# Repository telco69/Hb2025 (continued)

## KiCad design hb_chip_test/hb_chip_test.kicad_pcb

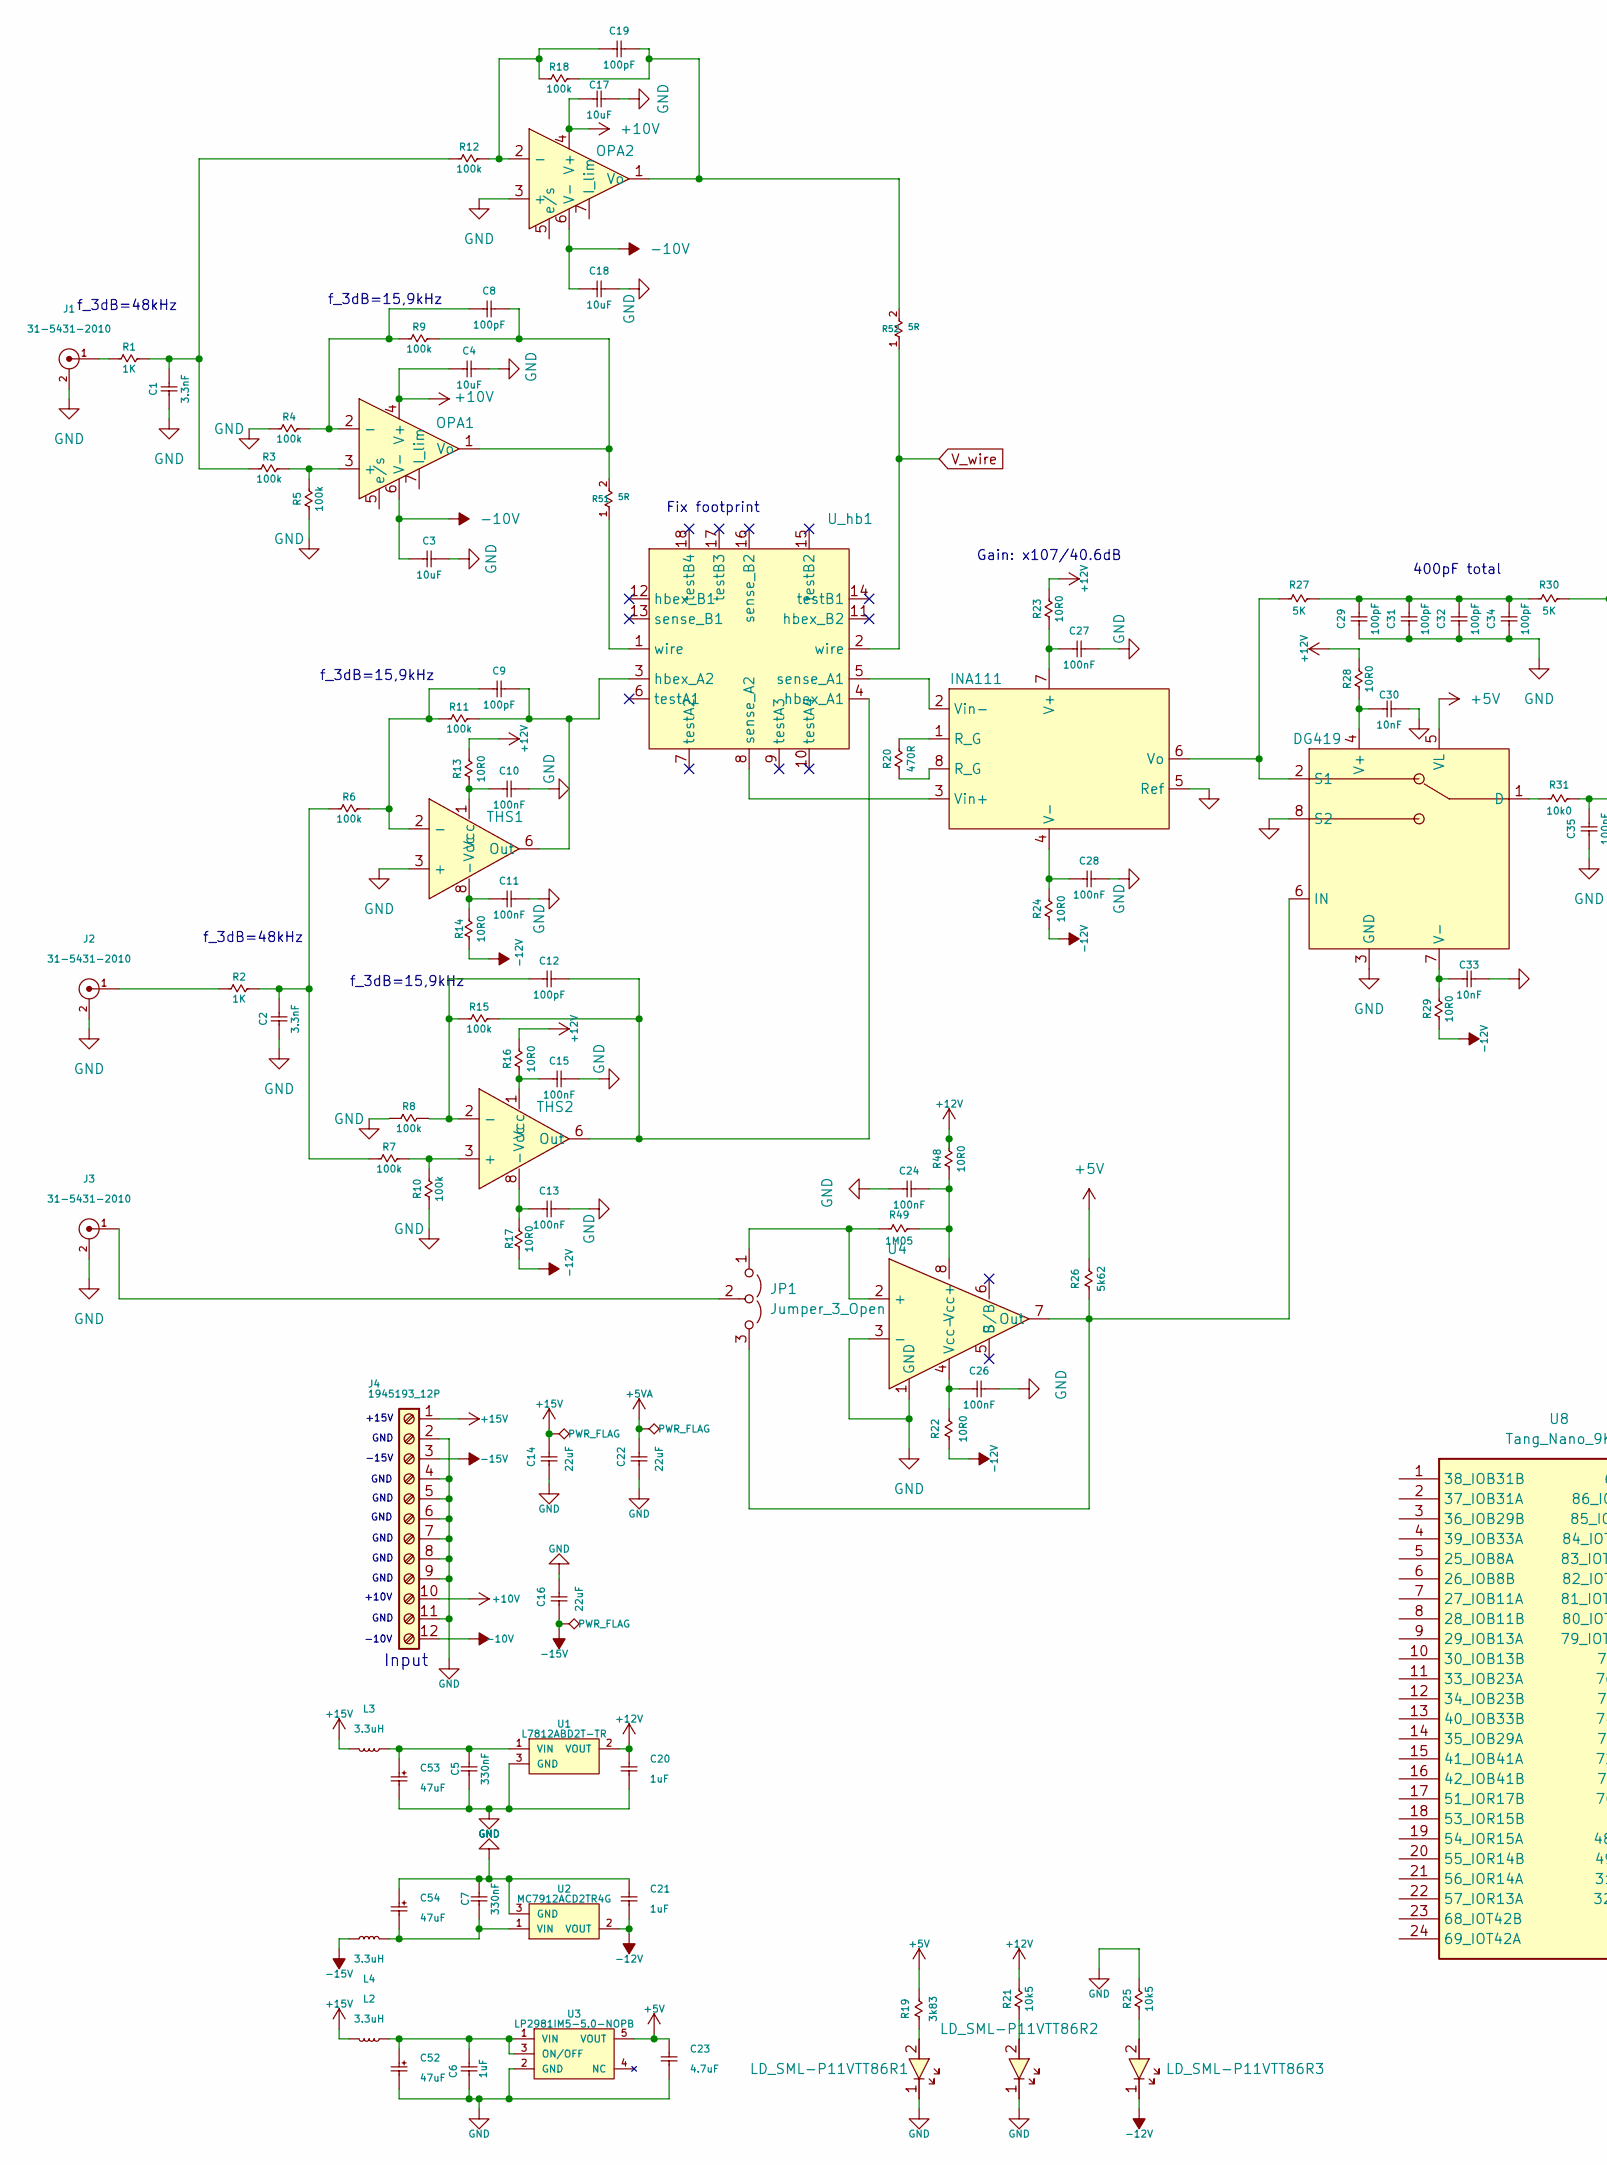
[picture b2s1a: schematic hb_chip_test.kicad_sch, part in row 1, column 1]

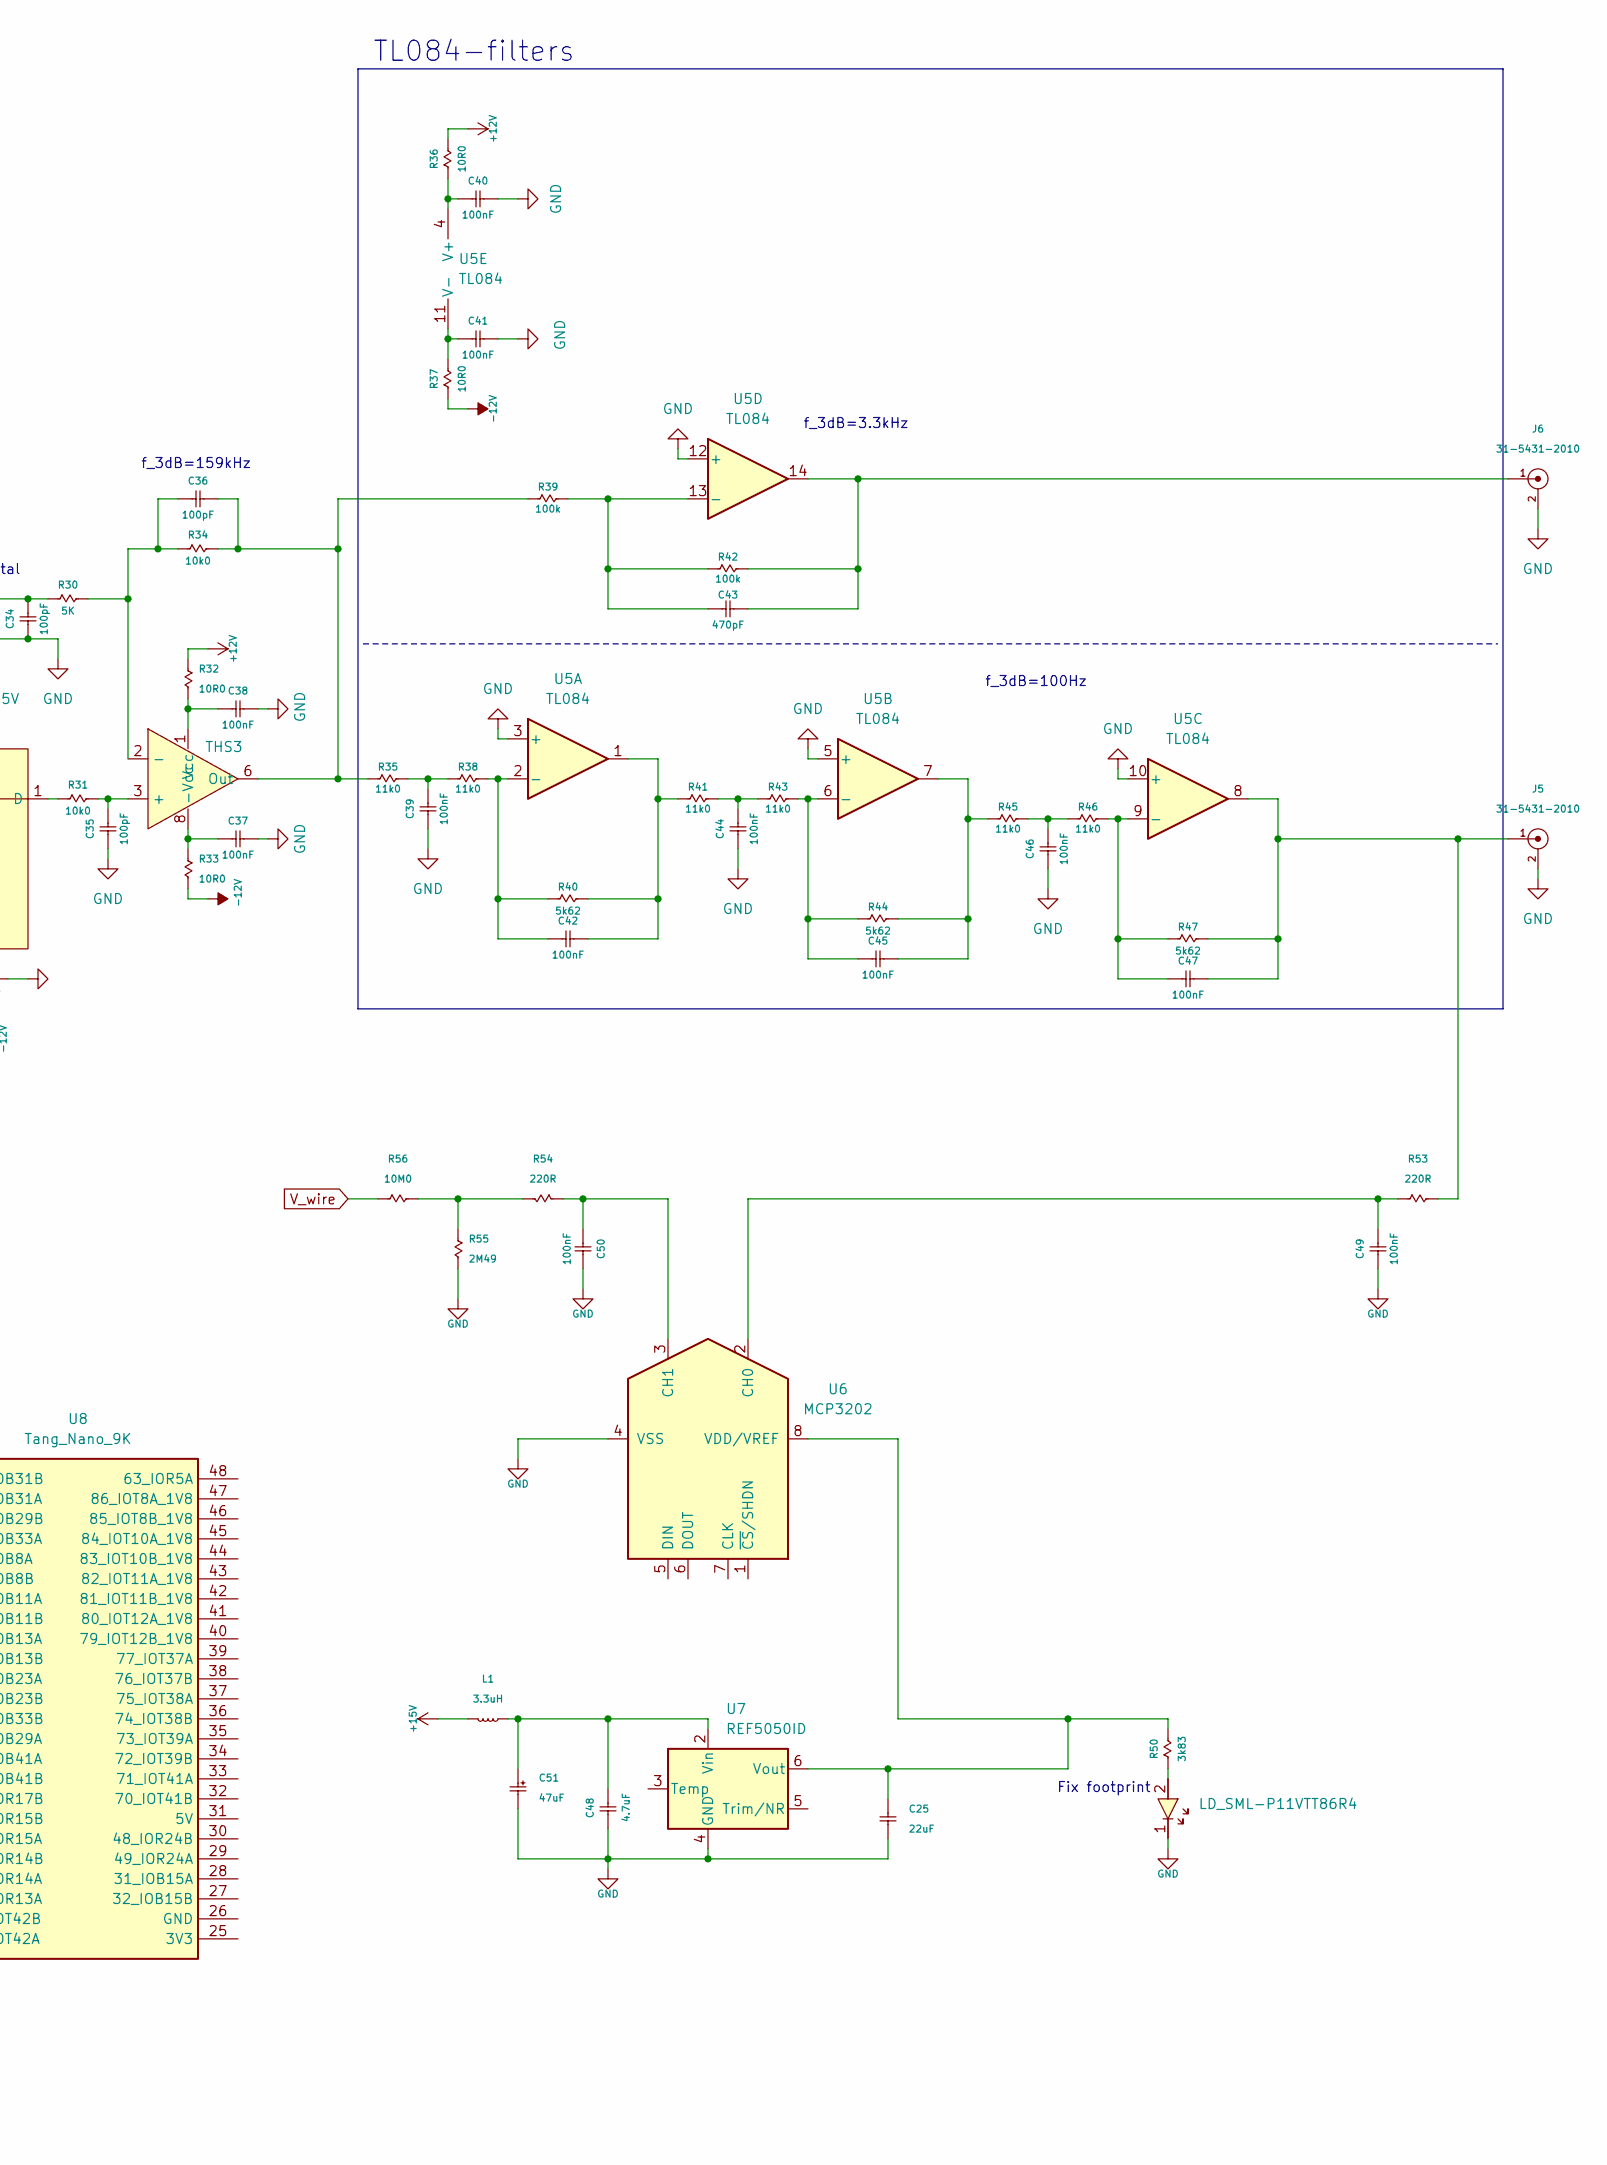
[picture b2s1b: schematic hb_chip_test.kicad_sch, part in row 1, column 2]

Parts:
C1, C2: C_0402_3.3nF_16V_X7R_CID1.2.2599; C0402_CAPC100X50X61L25N; Tolerance 5.0 %; Voltage 16.0 V; MPN 0402YC332JAT2A
C3, C4, C17, C18: C_2220_10uF_50V_X7R_CID1.2.4299; C2220_CAPC570X500X270L60N; Tolerance 5.0 %; Voltage 50.0 V; MPN 22205C106JAT2A
C5, C7: C_0805_330nF_50V_X7R_CID1.2.632; C0805_CAPC200X125X130L45N; MPN CL21B334KBFNNNE
C6, C20, C21: C_0805_1uF_16V_X7R_CID1.2.3095; C0805_CAPC200X125X130L45N; Tolerance 5.0 %; Voltage 16.0 V; MPN 0805YC105JAT2A
C8, C9, C12, C19, C29, C31, C32, C34, C35, C36: C_0402_100pF_50V_C0G_CID1.2.681; C0402_CAPC100X50X61L25N; Tolerance 5.0 %; Voltage 50.0 V; MPN 04025A101JAT2A
C10, C11, C13, C15, C24, C26, C27, C28, C37, C38, C39, C40, C41, C42, C44, C45, C46, C47, C49, C50: C_0805_100nF_16V_X7R_CID1.2.3078; C0805_CAPC200X125X130L45N; Tolerance 5.0 %; Voltage 16.0 V; MPN 0805YC104JAT2A
C14, C16, C22, C25: C_2220_22uF_25V_X7R_CID1.2.4254; C2220_CAPC570X500X270L60N; Tolerance 5.0 %; Voltage 25.0 V; MPN 22203C226JAT2A
C23, C48: C_1812_4.7uF_25V_X7R_CID1.2.4026; C1812_CAPC450X320X280L60N; Tolerance 5.0 %; Voltage 25.0 V; MPN 18123C475JAT2A
C30, C33: C_0402_10nF_16V_X7R_CID1.2.2607; C0402_CAPC100X50X61L25N; Tolerance 5.0 %; Voltage 16.0 V; MPN 0402YC103JAT2A
C43: C_0402_470pF_50V_C0G_CID1.2.184; C0402_CAPC100X50X61L25N; Capacitance Tolerance ±5%; Voltage Rating (DC) 50.0 V; MPN GCM1555C1H471JA16D
C51, C52, C53, C54: C_2917_47uF_20V_20%_CID1.3.892; C2917_CAPC730X430X310L130N; MPN 20TQC47MYFT
DG419: SOIC-8_3.9x4.9mm_P1.27mm
INA111: SMDIP-8_W9.53mm
J1, J2, J3, J5, J6: 31-5431-2010_CID2.5.196; AMPHENOL_31-5431-2010; MPN 31-5431-2010
J4: 1945193_12P_CID2.2.928; PHOENIX_1945193_12P; MPN 1945193_12P
JP1: Jumper_3_Open; 2_WAY_SOLDER_JUMPER
L1, L2, L3, L4: L_3.3uH_870mA_CID7.3.944; L0805_INDC200X125X140L50N; MPN BRC2012T3R3MD
LD_SML-P11VTT86R1, LD_SML-P11VTT86R2, LD_SML-P11VTT86R3, LD_SML-P11VTT86R4: SML_P11; MPN SML-P11VTT86R
OPA1, OPA2: TO-220-7_P2.54x3.8mm_StaggerOdd_Lead5.85mm_TabDown
R1, R2: R_0805_1K_CID10.99.611; R0805_RESC200X125X50L35N; MPN Y16291K00000B9R
R3, R4, R5, R6, R7, R8, R9, R10, R11, R12, R15, R18, R39, R42: R_0805_100k_CID10.9.5903; R0805_RESC200X125X50L35N; Tolerance 1.0 %; Voltage 50.0 V; MPN CRCW0805100KFKEA
R13, R14, R16, R17, R22, R23, R24, R28, R29, R32, R33, R36, R37, R48: R_0805_10R0_CID10.9.4757; R0805_RESC200X125X50L35N; Tolerance 1.0 %; Voltage 50.0 V; MPN 40010260210R0F4
R19, R50: R_0805_3k83_CID10.9.461; R0805_RESC200X125X50L35N; Power Rating 125.0 mW; Resistance Tolerance ±1%; MPN CRCW08053K83FKEA
R20: R_0402_470R_CID10.9.70; R0402_RESC100X50X37L20N; Power Rating 100.0 mW; Resistance Tolerance ±1%; MPN ERJ-2RKF4700X
R21, R25: R_0805_10k5_CID10.9.5868; R0805_RESC200X125X50L35N; Tolerance 1.0 %; Voltage 50.0 V; MPN CRCW080510K5FKEA
R26, R40, R44, R47: R_0805_5k62_CID10.9.159; R0805_RESC200X125X50L35N; Power Rating 125.0 mW; Resistance Tolerance ±1%; MPN CRCW08055K62FKEA
R27, R30: R_0805_5K_CID10.99.612; R0805_RESC200X125X50L35N; MPN Y16295K00000T9R
R31, R34: R_0805_10k0_CID10.9.476; R0805_RESC200X125X50L35N; Power Rating 125.0 mW; Resistance Tolerance ±1%; MPN CRCW080510K0FKEA
R35, R38, R41, R43, R45, R46: R_0805_11k0_CID10.9.5869; R0805_RESC200X125X50L35N; Tolerance 1.0 %; Voltage 50.0 V; MPN CRCW080511K0FKEA
R49: R_0805_1M05_CID10.9.5947; R0805_RESC200X125X50L35N; Tolerance 1.0 %; Voltage 50.0 V; MPN CRCW08051M05FKEA
R51, R52: 5R; TO-220-2_Horizontal_TabDown; MPN PWR220T-35-5R00F
R53, R54: R_0805_220R_CID10.9.602; R0805_RESC200X125X50L35N; Power Rating 125.0 mW; Resistance Tolerance ±1%; MPN CRCW0805220RFKEAHP
R55: R_0805_2M49_CID10.9.5964; R0805_RESC200X125X50L35N; Tolerance 1.0 %; Voltage 50.0 V; MPN CRCW08052M49FKEA
R56: R_0805_10M0_CID10.9.5993; R0805_RESC200X125X50L35N; Tolerance 1.0 %; Voltage 50.0 V; MPN CRCW080510M0FKEA
THS1, THS2, THS3: SOIC-8_3.9x4.9mm_P1.27mm
U1: L7812ABD2T-TR_CID8.52.934; DPAK3P508_1419X457L172X97T635X1023N; MPN L7812ABD2T-TR
U2: MC7912ACD2TR4G_CID8.52.429; DPAK3P508_1419X457L172X97T635X1023N; MPN MC7912ACD2TR4G
U3: LP2981IM5-5.0-NOPB_CID8.52.176; SOT23-5P95_270X145L35X35N; Current Rating 100.0mA; Dropout Voltage 200.0mV; MPN LP2981IM5-5.0-NOPB
U4: SO-8_3.9x4.9mm_P1.27mm; MPN LM311DT
U5: TL084; SOIC-14_3.9x8.7mm_P1.27mm
U6: MCP3202; SOIC-8_3.9x4.9mm_P1.27mm
U7: REF5050ID; SOIC-8_3.9x4.9mm_P1.27mm
U8: Tang_Nano_9K; DIP-48_TangNano9K
U_hb1: (no value)

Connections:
+5V: C23.1, DG419.5 (VL), R19.2, R26.2, U3.5 (VOUT); also elsewhere on the board
+5VA: C22.2
+10V: C4.1, C17.1, J4.10, OPA1.4 (V+), OPA2.4 (V+)
+12V: C20.1, R13.2, R16.2, R21.2, R23.2, R28.2, R32.1, R36.2, R48.2, U1.2 (VOUT)
+15V: C14.2, J4.1, L1.1, L2.1, L3.1
-10V: C3.1, C18.1, J4.12, OPA1.6 (V-), OPA2.6 (V-)
-12V: C21.2, LD_SML-P11VTT86R3.1, R14.1, R17.1, R22.1, R24.1, R29.1, R33.2, R37.1, U2.2 (VOUT)
-15V: C16.1, J4.3, L4.1
GND: C1.1, C2.1, C3.2, C4.2, C5.1, C6.2, C7.2, C10.2, C11.2, C13.2, C14.1, C15.2, C16.2, C17.2, C18.2, C20.2, C21.1, C22.1, C23.2, C24.1, C25.2, C26.2, C27.2, C28.2, C29.1, C30.2, C31.1, C32.1, C33.2, C34.1, C35.1, C37.2, C38.2, C39.1, C40.2, C41.2, C44.1, C46.1, C48.2, C49.1, C50.1, C51.2, C52.2, C53.2, C54.1, DG419.3 (GND), DG419.8 (S2), INA111.5 (Ref), J1.2, J2.2, J3.2, J4.2, J4.4, J4.5, J4.6, J4.7, J4.8, J4.9, J4.11, J5.2, J6.2, LD_SML-P11VTT86R1.1, LD_SML-P11VTT86R2.1, LD_SML-P11VTT86R4.1, OPA2.3 (+), R4.1, R5.1, R10.1, R25.2, R55.2, THS1.3 (+), U1.3 (GND), U2.3 (GND), U3.2 (GND), U4.1 (GND), U4.3 (-), U5.3 (+), U5.5 (+), U5.10 (+), U5.12 (+), U6.4 (VSS), U7.4 (GND)
unnamed: C1.2, R1.2, R3.1, R12.1
unnamed: C2.2, R2.2, R6.1, R7.1
unnamed: C29.2, C31.2, C32.2, C34.2, R27.2, R30.1
unnamed: C39.2, R35.2, R38.1
unnamed: C42.2, R40.2, R41.1, U5.1
unnamed: C43.2, J6.1, R42.2, U5.14
unnamed: C44.2, R41.2, R43.1
unnamed: C45.2, R44.2, R45.1, U5.7
unnamed: C46.2, R45.2, R46.1
unnamed: C47.2, J5.1, R47.2, R53.2, U5.8
unnamed: DG419.1 (D), R31.1
unnamed: DG419.6 (IN), JP1.3 (B), R26.1, U4.7 (Out)
unnamed: DG419.2 (S1), INA111.6 (Vo), R27.1
unnamed: C30.1, DG419.4 (V+), R28.1
unnamed: C33.1, DG419.7 (V-), R29.2
unnamed: INA111.1 (R_G), R20.2
unnamed: INA111.8 (R_G), R20.1
unnamed: C27.1, INA111.7 (V+), R23.1
unnamed: C28.1, INA111.4 (V-), R24.2
unnamed: INA111.3 (Vin+), U_hb1.8 (sense_A2)
unnamed: INA111.2 (Vin-), U_hb1.5 (sense_A1)
unnamed: J1.1, R1.1
unnamed: J2.1, R2.1
unnamed: JP1.1 (A), R49.1, U4.2 (+)
unnamed: J3.1, JP1.2 (C)
unnamed: LD_SML-P11VTT86R1.2, R19.1
unnamed: LD_SML-P11VTT86R2.2, R21.1
unnamed: LD_SML-P11VTT86R3.2, R25.1
unnamed: LD_SML-P11VTT86R4.2, R50.1
unnamed: OPA1.3 (+), R3.2, R5.2
unnamed: C8.1, OPA1.2 (-), R4.2, R9.1
unnamed: C8.2, OPA1.1 (Vo), R9.2, R51.2
unnamed: C19.1, OPA2.2 (-), R12.2, R18.1
unnamed: C19.2, OPA2.1 (Vo), R18.2, R52.2
unnamed: R51.1, U_hb1.1 (wire)
unnamed: R54.2, R55.1, R56.2
unnamed: C9.1, R6.2, R11.1, THS1.2 (-)
unnamed: C11.1, R14.2, THS1.8 (-Vcc)
unnamed: C9.2, R11.2, THS1.6 (Out), U_hb1.3 (hbex_A2)
unnamed: C10.1, R13.1, THS1.1 (Vcc)
unnamed: R7.2, R10.2, THS2.3 (+)
unnamed: C12.1, R15.1, THS2.2 (-)
unnamed: C13.1, R17.2, THS2.8 (-Vcc)
unnamed: C12.2, R15.2, THS2.6 (Out), U_hb1.4 (hbex_A1)
unnamed: C15.1, R16.1, THS2.1 (Vcc)
unnamed: C35.2, R31.2, THS3.3 (+)
unnamed: C36.1, R30.2, R34.1, THS3.2 (-)
unnamed: C37.1, R33.1, THS3.8 (-Vcc)
unnamed: C36.2, R34.2, R35.1, R39.1, THS3.6 (Out)
unnamed: C38.1, R32.2, THS3.1 (Vcc)
unnamed: C5.2, C53.1, L3.2, U1.1 (VIN)
unnamed: C7.1, C54.2, L4.2, U2.1 (VIN)
unnamed: C6.1, C52.1, L2.2, U3.1 (VIN), U3.3 (ON/OFF)
unnamed 62: C24.2, R48.1, R49.2, U4.8 (Vcc+); also elsewhere on the board
unnamed: C26.1, R22.2, U4.4 (Vcc-)
unnamed: C42.1, R38.2, R40.1, U5.2 (-)
unnamed: C45.1, R43.2, R44.1, U5.6 (-)
unnamed: C47.1, R46.2, R47.1, U5.9 (-)
unnamed: C43.1, R39.2, R42.1, U5.13 (-)
unnamed: C40.1, R36.1, U5.4 (V+)
unnamed: C41.1, R37.2, U5.11 (V-)
unnamed: C49.2, R53.1, U6.2 (CH0)
unnamed: C50.2, R54.1, U6.3 (CH1)
unnamed: C25.1, R50.2, U6.8 (VDD/VREF), U7.6 (Vout)
unnamed: C48.1, C51.1, L1.2, U7.2 (Vin)
V_wire: R52.1, R56.1, U_hb1.2 (wire)

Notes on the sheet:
f_3dB=48kHz
Input
GND
+15V
Fix footprint
-15V
f_3dB=100Hz
f_3dB=159kHz
-10V
f_3dB=15,9kHz
TL084-filters
+10V
f_3dB=3.3kHz
400pF total
Gain: x107/40.6dB

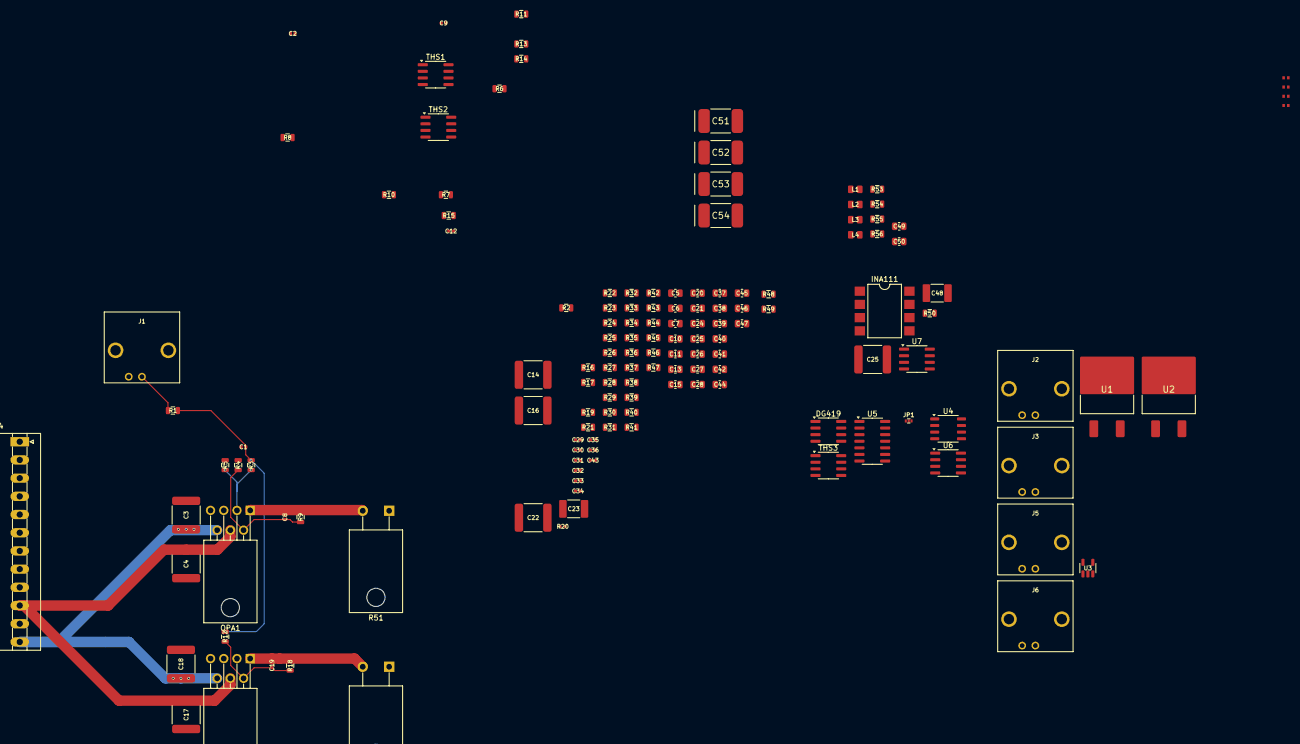
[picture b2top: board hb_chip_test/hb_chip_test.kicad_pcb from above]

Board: 2 copper layers, 140 parts (0 on the bottom side), 71 nets.

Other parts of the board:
C25#2: C_0805_100nF_16V_X7R_CID1.2.3078; C0805_CAPC200X125X130L45N

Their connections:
+5V: C25#2.2; also elsewhere on the board
unnamed 62: C25#2.1; also elsewhere on the board

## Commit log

2025-03-31 First push
2025-04-03 Filters and tang nano 9k
2025-04-04 Variable amps and offset circuit
2025-04-04 BNC added
2025-04-12 HB driver jumpers + PCBv1
    TangNano9k has been wired.
    Jumpers place for the hb drive but no bnc's for this. If something else is to drive it it can be done from jumpers.
    PCB is in the layout v1 now. Still missing socket for the chip.
2025-04-15 PCBv2
    Room for heatsinks, wiring corrections.
